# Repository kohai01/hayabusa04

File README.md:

# hayabusa04
 macropad with 4 keys

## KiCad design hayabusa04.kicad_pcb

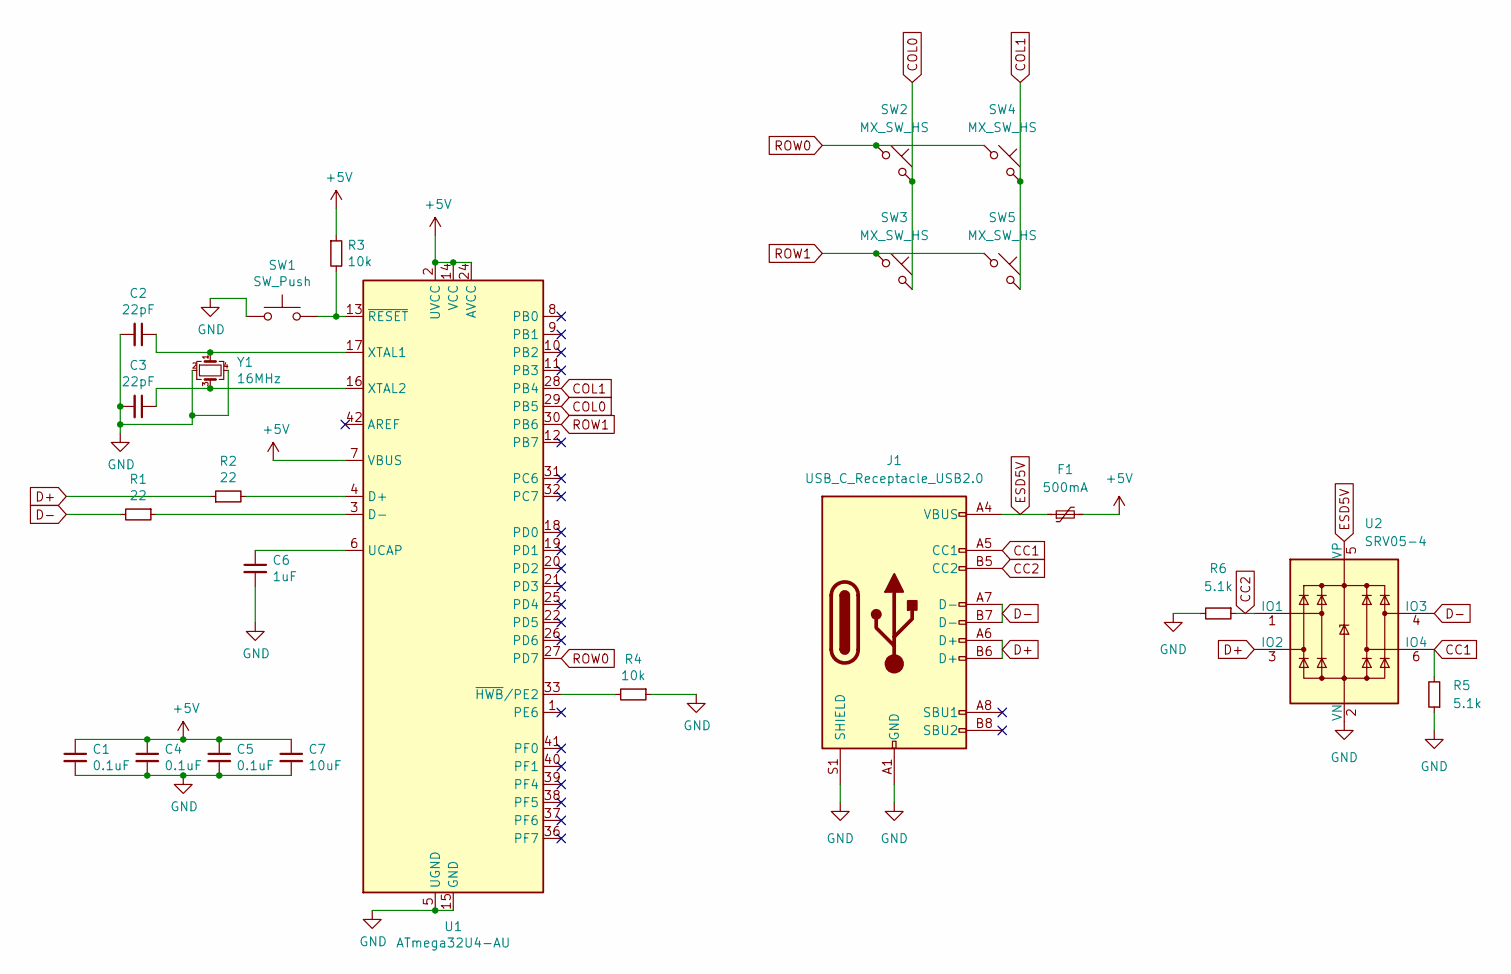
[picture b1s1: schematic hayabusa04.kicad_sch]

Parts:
C1, C4, C5: 0.1uF; C_0805_2012Metric
C2, C3: 22pF; C_0805_2012Metric
C6: 1uF; C_0805_2012Metric
C7: 10uF; C_0805_2012Metric
F1: 500mA; Fuse_1206_3216Metric
J1: USB_C_Receptacle_USB2.0; USB_C_Receptacle_HRO_TYPE-C-31-M-12
R1, R2: 22; R_0805_2012Metric
R3, R4: 10k; R_0805_2012Metric
R5, R6: 5.1k; R_0805_2012Metric
SW1: SW_Push; SKQG-1155865
SW2, SW3, SW4, SW5: MX_SW_HS; SW_MX_HS_1u
U1: ATmega32U4-AU; TQFP-44_10x10mm_P0.8mm
U2: SRV05-4; SOT-23-6
Y1: 16MHz; Crystal_SMD_3225-4Pin_3.2x2.5mm

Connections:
+5V: C1.1, C4.1, C5.1, C7.1, F1.2, R3.1, U1.2 (UVCC), U1.7 (VBUS), U1.14 (VCC), U1.24 (AVCC), U1.34 (VCC), U1.44 (AVCC)
CC1: J1.A5 (CC1), R5.2, U2.6 (IO4)
CC2: J1.B5 (CC2), R6.1, U2.1 (IO1)
COL0: SW2.2, SW3.2, U1.29 (PB5)
COL1: SW4.2, SW5.2, U1.28 (PB4)
D+: J1.A6 (D+), J1.B6 (D+), R2.1, U2.3 (IO2)
D-: J1.A7 (D-), J1.B7 (D-), R1.2, U2.4 (IO3)
ESD5V: F1.1, J1.A4 (VBUS), J1.A9 (VBUS), J1.B4 (VBUS), J1.B9 (VBUS), U2.5 (VP)
GND: C1.2, C2.2, C3.2, C4.2, C5.2, C6.2, C7.2, J1.A1 (GND), J1.A12 (GND), J1.B1 (GND), J1.B12 (GND), J1.S1 (SHIELD), R4.1, R5.1, R6.2, SW1.1, U1.5 (UGND), U1.15 (GND), U1.23 (GND), U1.35 (GND), U1.43 (GND), U2.2 (VN), Y1.2, Y1.4
unnamed: C2.1, U1.17 (XTAL1), Y1.1
unnamed: C3.1, U1.16 (XTAL2), Y1.3
unnamed: C6.1, U1.6 (UCAP)
unnamed: R1.1, U1.3 (D-)
unnamed: R2.2, U1.4 (D+)
unnamed: R3.2, SW1.2, U1.13 (~RESET)
unnamed: R4.2, U1.33 (~HWB/PE2)
ROW0: SW2.1, SW4.1, U1.27 (PD7)
ROW1: SW3.1, SW5.1, U1.30 (PB6)

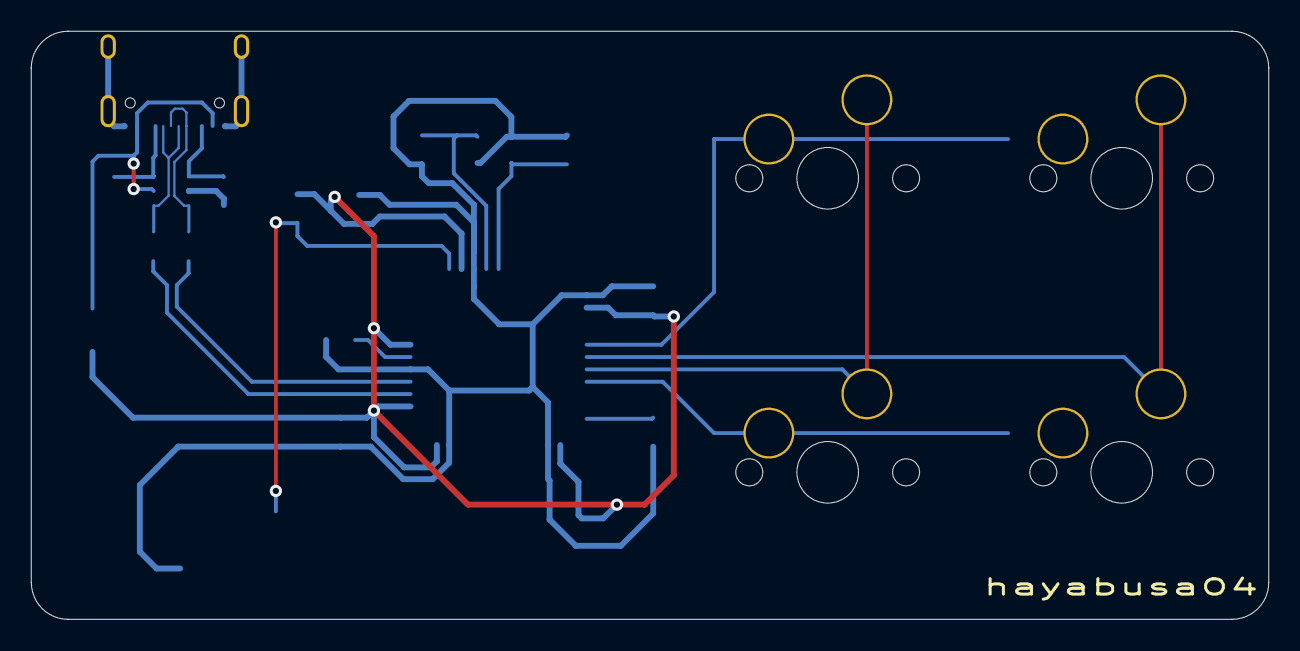
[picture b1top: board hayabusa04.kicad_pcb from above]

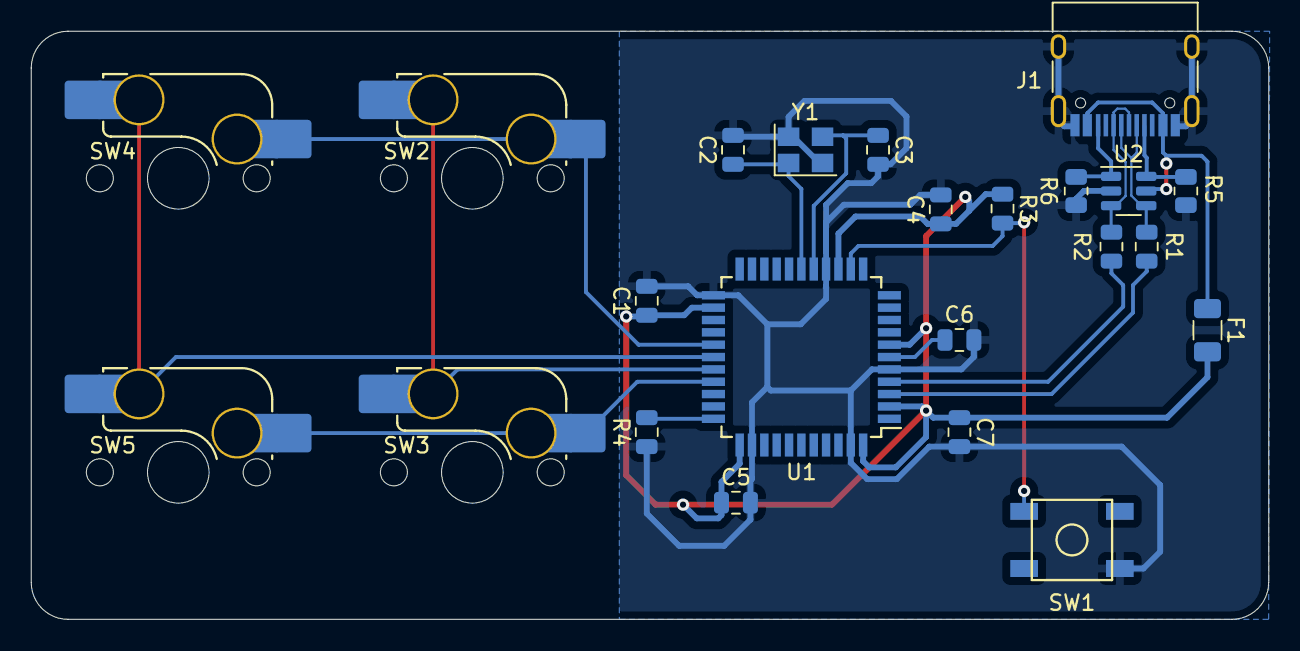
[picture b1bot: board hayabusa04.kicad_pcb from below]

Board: 2 copper layers, 80.2 x 38.1 mm, 23 parts (23 on the bottom side), 18 nets.

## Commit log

2022-10-10 add submodules
2022-10-10 add footprint libraries
2022-10-10 add schematic
2022-10-13 prepared the pcb
2022-10-13 routed pcb
2022-10-13 updated pcb
2022-10-15 test
2022-10-22 hotswap compatible
2022-10-28 updated silk screen
2022-10-31 routed usb c
2022-10-31 generated gerber files
2022-11-07 added 3d models
2022-11-07 updated silk screen text
2022-12-11 initial commit after clean up
